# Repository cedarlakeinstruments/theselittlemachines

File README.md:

## [Thermometer simulator ](https://github.com/cedarlakeinstruments/theselittlemachines/edit/main/README.md#thermometer-simulator)

Simple digital thermometer simulator based on Raspberry Pi Pico and
a Sparkfun SSD1306-type OLED connected via I2C. Of course, the code's written in Python ;-)

You can download it [here](code/code.py)

The desire is to display a temperature that is adjustable in 0.1 degree increments by pushbuttons. The pushbuttons are connected between Ground and GP7 & GP8.
At least, that was the intent. However, my ham-fisted soldering connected the common to GP9 instead of GND. 

No problem, though. We'll just turn GP9 into an output and pull it to GND. Accomplishes the same thing and I don't have to fix my wiring :-)

~~~
# Code designed for Raspberry Pi Pico running CircuitPython 9.2
# Simulates a digital thermometer using an OLED for display

# Imports
import time 
import random
import board
import busio
import digitalio
from adafruit_debouncer import Debouncer
import displayio
import terminalio
import adafruit_displayio_ssd1306 as ssd1306
from adafruit_display_text import label

# Compatibility with both CircuitPython 8.x.x and 9.x.x.
# Remove after 8.x.x is no longer a supported release.
try:
    from i2cdisplaybus import I2CDisplayBus
    print ("Imported from i2cdisplaybus")
except ImportError:
    from displayio import I2CDisplay as I2CDisplayBus
    print ("Imported from displayio")
    
# Reinitalizes display upon any soft reboot or hard reset
displayio.release_displays()

# Set up I2C and the pins we're using for it
i2c0 = busio.I2C(scl=board.GP1, sda=board.GP0)

# Short delay to stop I2C falling over
time.sleep(1) 

# Configure display size
ssd_width = 128
ssd_height = 32

# Ensure the physical address of your SSD1306 is set here:
ssd_bus = I2CDisplayBus(i2c0, device_address=0x3C)
display = ssd1306.SSD1306(ssd_bus, width=ssd_width, height=ssd_height)

# Text labels for display
temp_label = label.Label(terminalio.FONT)
temp_label.anchor_point = (0.0, 0.0)
temp_label.anchored_position = (0, 10)
temp_label.scale = 2

# Create DisplayIO Group Layer
layer1 = displayio.Group()
layer1.append(temp_label)
display.root_group = layer1

# Pushbuttons on pins 7 & 8
up_pin = digitalio.DigitalInOut(board.GP8)
up_pin.direction = digitalio.Direction.INPUT
up_pin.pull = digitalio.Pull.UP
buttonUp = Debouncer(up_pin)

down_pin = digitalio.DigitalInOut(board.GP7)
down_pin.direction = digitalio.Direction.INPUT
down_pin.pull = digitalio.Pull.UP
buttonDown = Debouncer(down_pin)

# debug due to my wiring screwup
gnd = digitalio.DigitalInOut(board.GP9)
gnd.direction = digitalio.Direction.OUTPUT
gnd.value = False

temp = 37.0
last_temp = 0.0
# Constants
TEMP_INCREMENT = 0.1
TEMP_MIN = 30
TEMP_MAX = 40

while True:
    buttonUp.update()
    buttonDown.update()
    # Check button change state
    if buttonDown.fell:
        temp -= TEMP_INCREMENT
        print(temp)
    elif buttonUp.fell:
        temp += TEMP_INCREMENT
        print(temp)
        
    if temp < TEMP_MIN:
        temp = TEMP_MIN
    elif temp > TEMP_MAX:
        temp = TEMP_MAX
    
    # Only update on a change
    if last_temp != temp:
        # Format for display   
        temp_label.text = f"Temp {temp:.1f}C"
        last_temp = temp
~~~

---

## [Ball Speed Project](https://github.com/cedarlakeinstruments/theselittlemachines/edit/main/README.md#ballSpeed)

This project measures the speed of a ball and takes actions depending on how fast it's going. It plays audio feedback depending on the speed of the ball.
Code is [here](https://github.com/cedarlakeinstruments/theselittlemachines/tree/main/BallSpeed)

---

## [High/Low solenoid driver](https://github.com/cedarlakeinstruments/theselittlemachines/main/README.md#hi-lo)

Driving solenoids is pretty easy. Just need a single digital pin and a motor or solenoid driver. Since it takes more energy to activate the
solenoid than to keep it on, we can apply this method if we need to save power.
We'll activate the solenoid at full power for about a quarter second (or however long it takes it to move into position, then drop
the output level by PWM).

You can download it [here](code/solenoid/solenoid.ino)

---
## [Liquid Level Sensor ](https://github.com/cedarlakeinstruments/theselittlemachines/main/README.md#level)
How to detect the liquid surface when filling a syrup bottle. Simple liquid level sensor senses conductivity using two food-safe
stainless steel probes.
An Arduino Nano drives the probes with a low-current signal, using the fluid to provide conductivity. Two analog inputs are used to detect the current flow
through the liquid. By switching the current back and forth, we can prevent mineral buildup on the probes.

When the measured signal crosses a threshold, we turn on an output to indicate that the level is detected. The output can stop a pump, or trigger an indicator to the
operator.

Download the code [here](LiquidLevelSensor/LiquidLevelSensor.ino)

Schematic diagram

Contact me: <littlemachines@cedarlakeinstruments.com>

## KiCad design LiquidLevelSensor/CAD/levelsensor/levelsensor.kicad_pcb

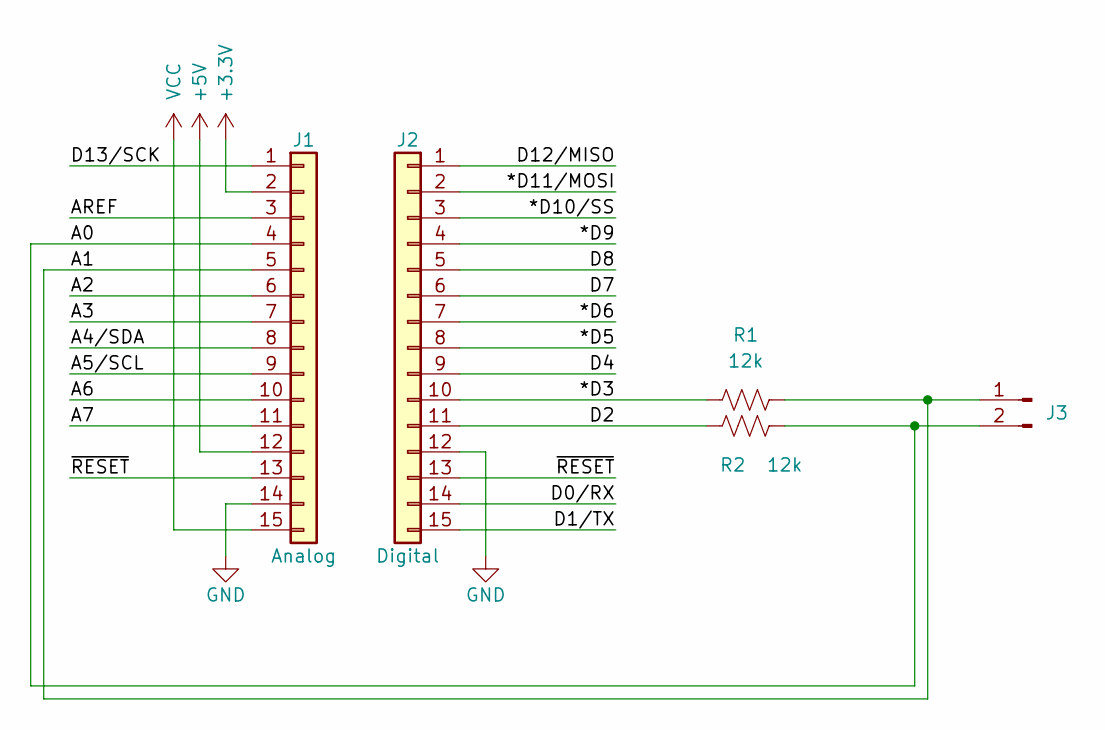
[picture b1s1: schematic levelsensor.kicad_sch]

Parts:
J1: Analog; PinHeader_1x15_P2.54mm_Vertical
J2: Digital; PinHeader_1x15_P2.54mm_Vertical
J3: Conn_01x02_Male
R1, R2: 12k; R_0805_2012Metric_Pad1.20x1.40mm_HandSolder

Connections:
+3V3: J1.2
+5V: J1.12
/*D3: J2.10, R1.1
/*D5: J2.8
/*D6: J2.7
/*D9: J2.4
/*D10/SS: J2.3
/*D11/MOSI: J2.2
/A0: J1.4, J3.2, R2.2
/A1: J1.5, J3.1, R1.2
/A2: J1.6
/A3: J1.7
/A4/SDA: J1.8
/A5/SCL: J1.9
/A6: J1.10
/A7: J1.11
/AREF: J1.3
/D0/RX: J2.14
/D1/TX: J2.15
/D2: J2.11, R2.1
/D4: J2.9
/D7: J2.6
/D8: J2.5
/D12/MISO: J2.1
/D13/SCK: J1.1
/~RESET: J1.13, J2.13
GND: J1.14, J2.12
VCC: J1.15

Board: 2 copper layers, 9 parts (2 on the bottom side), 6 nets, no tracks yet.

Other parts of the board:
MH1, MH2, MH3, MH4: MountingHole_65mil

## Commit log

2022-08-09 Added audio
    Interfaced DF Robot MP3 player over software serial.
2022-08-13 Added kicad schematic
2022-08-15 Added support for "balls gone" sensor.
2022-09-03 Support for Player Mini
    Untested support for DF Player Mini
2022-09-07 Documentation updates
    Better explanation of user adjustments,
    Fixed potential array out of bounds
2022-09-12 v1.2
    Individual flash times
    Delay after ball detected
2023-03-13 Added cue ball sensors and relay
2023-03-13 Added more sensors and updated comments
2023-03-24 Added delay for laser sensor to settle.
2023-12-07 Create CNAME
2023-12-07 Update CNAME
2024-08-03 Test code & image tags
2024-08-03 Fix readme bug
2024-08-06 Added jpg
2024-08-06 Added image
2024-08-06 Moved images. Added thermometer.
2024-08-06 Moved stuff around
2024-08-06 Changed link to image
2024-08-06 Testing markdown
2024-08-06 Renamed folder
2024-08-06 Learning more about markdown
    I should probably make these changes on a branch from now on...
2024-08-06 Pushbutton handling
2024-08-07 Updated code, changed layout.
2024-08-07 Updated code and image
2024-08-08 cleanup
2024-08-08 Removed customer info
2024-08-08 more cleanup
2024-08-14 Added Freelancer theme
2024-08-14 Added theme
2024-08-14 removed folder
2024-08-14 removed index.html
2024-08-14 removed freelancer files
2024-08-14 replaced images
2024-09-07 Update README.md
    Solenoid drive draft
2024-09-09 Update README.md
    Fixed link
2024-10-26 Update _config.yml
    Added google analytics
2024-11-01 Added new project
2024-11-01 Added CAD drawing
2024-11-02 Add liquid level sensor
2024-11-02 updated drawing
2024-11-02 Added photo
2024-11-02 Add liquid sensor picture
2024-11-14 added email link
